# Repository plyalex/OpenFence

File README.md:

#OpenFence
OpenFence is a digital livestock fencing system, which uses GPS and stereo audio alerts to contain animals within a specified boundary. 
The location of the fences can be updated using the web interface, and transferred to collar devices wirelessly using LoRa via the in field base station. 
The movements of the animals are logged and transferred to the web, to allow analysis of movements and land utilisation.
#The Purpose
OpenFence is designed to make it easier to implement productive and environmentally friendly grazing practises, such as cell grazing. 
This style of grazing has been shown to increase biodiversity, ground cover, soil carbon and water retention, however it is not commonly implemented due to the additional expenses of fencing and labour.
#Build Details
Go to the [HackaDay.io Page](https://hackaday.io/project/10725-openfence-digital-livestock-fencing)

#[Collar Code](https://github.com/plyalex/OpenFence/tree/master/software/collar/CollarSoftware)
Download and open with Arduino. Additional libraries required are: [TinyGPS++](https://github.com/mikalhart/TinyGPSPlus/releases) and RTCZero.

#Licence
All files: GNU GPL v3

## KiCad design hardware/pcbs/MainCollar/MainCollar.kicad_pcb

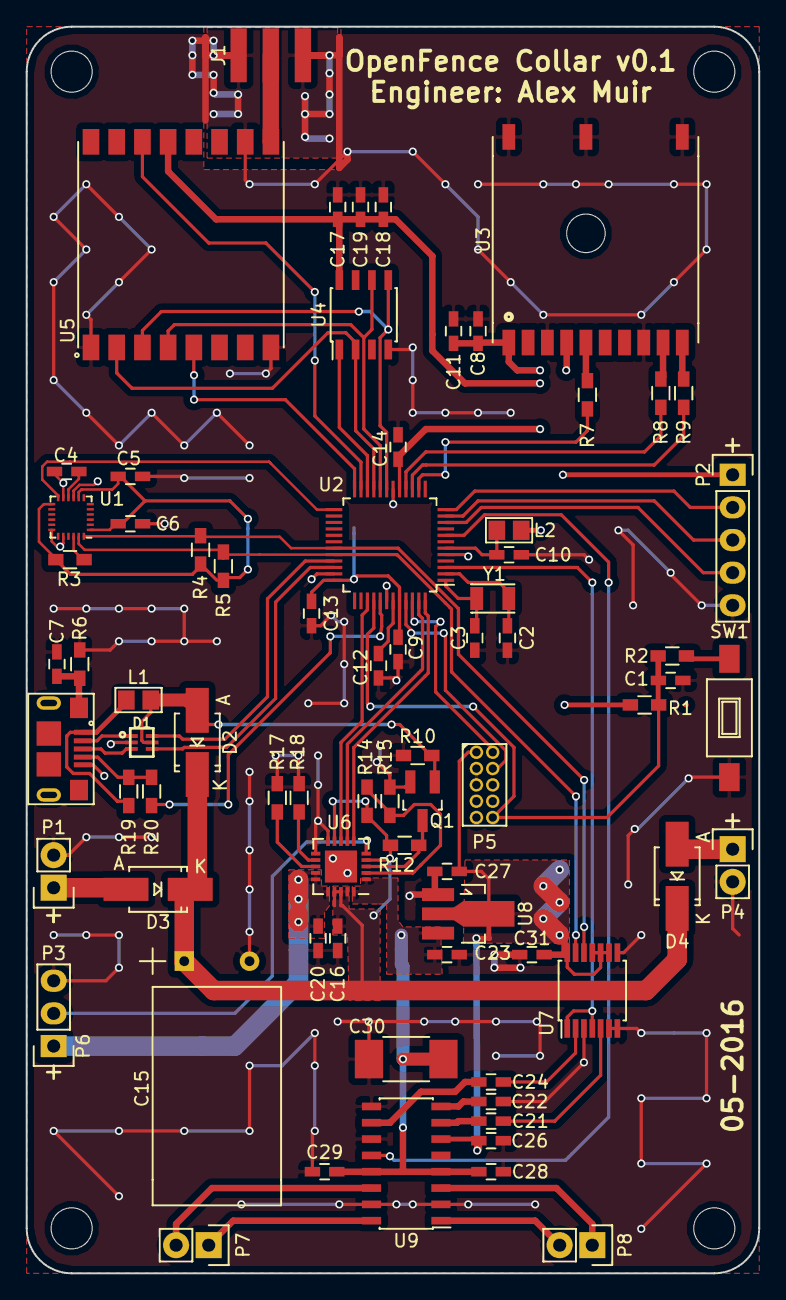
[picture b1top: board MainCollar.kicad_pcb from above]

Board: 2 copper layers, 57.0 x 97.0 mm, 78 parts (0 on the bottom side), 64 nets.

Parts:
C1, C4, C6, C9, C10, C13, C14, C17, C18, C31: 0.1uF; C_0603_HandSoldering
C2, C3: 18pF; C_0603_HandSoldering
C5, C11: 0.01uF; C_0603_HandSoldering
C7, C16, C19, C20, C23: 4.7uF; C_0603_HandSoldering
C8, C12, C22, C26, C27, C28, C29: 1uF; C_0603_HandSoldering
C15: 2200uF; Cap1017
C21, C24: 0.47uF; C_0603_HandSoldering
C30: 47uF; C_1812_HandSoldering
D1: USBLC6-2; SOT666
D2, D3, D4: SS24; SMA_Handsoldering
J1: SMA-EDGE; RF-SMA-EDGE
L1, L2: 600R @ 100MHz; IND-0805
M1, M2, M3, M4: Mounting_Hole; MountingHole_3.2mm_M3
P1: USB_OTG; USB-10118193-0001LF
P2: CONN_01X05; Pin_Header_Straight_1x05
P3: Solar1; Pin_Header_Straight_1x02
P4: Solar2; Pin_Header_Straight_1x02
P5: CONN_02X05; HDR_2x5_Pitch1.27mm
P6: Battery; Pin_Header_Straight_1x03
P7: SPK_L; Pin_Header_Straight_1x02
P8: SPK_R; Pin_Header_Straight_1x02
Q1: 2N7002; SOT-23_Handsoldering
R1, R3, R4, R5, R12: 10K; R_0603_HandSoldering
R2, R20: 330; R_0603_HandSoldering
R6: 1M; R_0603_HandSoldering
R7, R8, R9, R17: 1K; R_0603_HandSoldering
R10, R15, R19: 100K; R_0603_HandSoldering
R14: 270K; R_0603_HandSoldering
R18: 50K; R_0603_HandSoldering
SW1: SW_PUSH; SW_SPST_FSMSM
U1: MPU9250
U2: SAMD21G; TQFP-48_7x7mm_Pitch0.5mm
U3: PA6C
U4: S25FL116K; SOIC-8_3.9x4.9mm_Pitch1.27mm
U5: RF95W; RFM9xW
U6: MCP73871; QFN-20-1EP_4x4mm_Pitch0.5mm
U7: MAX5387; TSSOP-14_4.4x5mm_Pitch0.65mm
U8: MCP1700T-3302E/MB; SOT89-3_Housing_Handsoldering
U9: PAM8403; SOIC-16_3.9x9.9mm_Pitch1.27mm
Y1: 32.768kHz; FC-135

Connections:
+3V3: C5.1, C6.1, C8.1, C9.1, C11.1, C13.1, C14.1, C17.1, C18.1, C19.1, C26.1, C27.1, C31.2, L2.2, P2.1, P5.1, R1.1, R3.1, R4.1, R5.1, U1.1, U1.8, U1.13, U2.17, U2.36, U2.44, U3.1, U3.4, U4.8, U5.13, U7.9, U7.10, U7.11, U7.14, U8.2, U9.6
/AMP_SD: U2.8, U9.12
/AUX_1: P2.4, U2.10
/AUX_2: P2.3, U2.11
/AUX_3: P2.2, U2.12
/AudioIn: U2.3, U7.1, U7.4
/Flash_CS: U2.22, U4.1
/GPS_FIX: R7.1, U2.14
/GPS_RXD: R9.2, U2.15
/GPS_TXD: R8.1, U2.16
/MISO: U2.21, U4.2, U5.2
/MOSI: U2.19, U4.5, U5.3
/MPU_INT: U1.12, U2.25
/RF_CS: U2.24, U5.5
/RF_INT: U2.23, U5.14
/SCK: U2.20, U4.6, U5.4
/SCL: R5.2, U1.23, U2.32, U7.13
/SDA: R4.2, U1.24, U2.31, U7.12
/STAT1: U2.39, U6.8
/STAT2: U2.47, U6.7
/SWDCLK: P5.4, U2.45
/SWDIO: P5.2, U2.46
/USB+: D1.4, U2.34
/USB-: D1.6, U2.33
/USB_ID: R20.1, U2.41
/~PG: U2.48, U6.6
/~RESET~: C1.1, P5.10, R1.2, R2.1, U2.40
GND: C1.2, C2.1, C3.1, C4.2, C5.2, C6.2, C7.2, C8.2, C9.2, C10.2, C11.2, C12.2, C13.2, C14.2, C15.2, C16.2, C17.2, C18.2, C19.2, C20.2, C22.2, C23.2, C26.2, C27.2, C28.2, C29.2, C30.2, C31.1, D1.2, J1.2, J1.3, J1.4, J1.5, P1.5, P2.5, P3.2, P4.2, P5.3, P5.5, P6.3, Q1.2, R6.2, R10.2, R15.2, R17.2, R18.2, SW1.1, U1.9, U1.11, U1.18, U1.20, U2.5, U2.18, U2.35, U2.42, U3.3, U3.8, U3.11, U3.12, U3.13, U4.4, U5.1, U5.8, U5.10, U6.10, U6.11, U6.21, U7.3, U7.6, U7.7, U7.8, U8.1, U9.2, U9.9, U9.11, U9.15
unnamed: C2.2, U2.2, Y1.1
unnamed: C3.2, U2.1, Y1.2
unnamed: C4.1, U1.10
unnamed: C7.1, P1.6, R6.1
unnamed: C10.1, L2.1, U2.6
unnamed: C12.1, U2.43
unnamed: C21.1, U9.7
unnamed: C21.2, U7.5
unnamed: C22.1, U9.8
unnamed: C24.1, U9.10
unnamed: C24.2, U7.2
unnamed: D1.1, P1.2
unnamed: D1.3, P1.3
unnamed: D3.2, P3.1
unnamed: D4.2, P4.1
unnamed: J1.1, U5.9
unnamed: P1.4, R19.1, R20.2
unnamed: P6.2, U6.5
unnamed: P7.1, U9.16
unnamed: P7.2, U9.14
unnamed: P8.1, U9.3
unnamed: P8.2, U9.1
unnamed: Q1.3, R12.2, U6.3
unnamed: R2.2, SW1.2
unnamed: R3.2, U1.22
unnamed: R7.2, U3.5
unnamed: R8.2, U3.9
unnamed: R9.1, U3.10
unnamed: R14.2, R15.1, U6.2
unnamed: R17.1, U6.13
unnamed: R18.1, U6.12
VBAT: C20.1, P6.1, U6.14, U6.15, U6.16
VBUS: D1.5, D2.2, L1.2, Q1.1, R10.1
VCC: C15.1, C16.1, D2.1, D3.1, D4.1, R12.1, R14.1, U6.4, U6.9, U6.17, U6.18, U6.19
VOUT: C23.1, C28.1, C29.1, C30.1, U6.1, U6.20, U8.3, U9.4, U9.13
VUSB: L1.1, P1.1, R19.2

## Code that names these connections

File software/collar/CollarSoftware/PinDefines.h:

#ifndef PinDefines_h
#define PinDefines_h
	#include "Geofence.h"

	//I2C Addresses: MPU 0x68, POT 0x2F
	//GPS_TX, RX = Serial1
	//Serial Monitor = SerialUSB

	#define DAC_OUT     A0
	#define AMP_EN      A2
	#define AUX_0       9
	#define AUX_1       8
	#define AUX_2       A4
	#define GPS_FIX     3
	#define FLASH_CS    ATN
	#define RF_INT      2
	#define RF_CS       5
	#define MPU_INT     11
	#define CHARGE_S1   26 //PIN_LED_TXL
	#define CHARGE_S2   A5
	#define CHARGE_PG   25 //PIN_LED_RXL

	#define GPSSerial 	Serial1
	
	//Global Variables - Updatable in Web Interface
	extern uint8_t NODE_ADDRESS;
	extern uint8_t distThresh;
	extern uint8_t motionThresh;
	extern bool testing;
	extern int16_t magbias0;
	extern int16_t magbias1;
	extern int16_t magbias2;

	extern uint8_t polyCorners;
    extern struct position fencePoints[256];
    extern uint8_t fenceversion;

#endif

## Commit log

2016-04-21 Initial commit.
2016-04-21 Added links
2016-04-22 Added compiled file to the git ignore
2016-05-12 Schematics almost complete
2016-05-12 Creating an Arduino library for the PA6C GPS
2016-05-14 Initial PCB component placement
2016-05-16 PCB Prototype Completed
2016-05-18 Initial prototype design ready for 3D printing.
2016-05-20 Version 2 renders
2016-05-26 Second version ready for 3D printing.
2016-05-26 Renders for displaying the PCB
2016-05-26 Initial Commit of the geofence library
2016-05-26 Moving from doubles to floats
2016-08-14 Initial Commit of Web App
2016-08-14 Updating for mistakes
2016-08-14 Updating for custom PCB
2016-08-15 Added Tilt corrected compass heading.
    Using the function getHeading() will return a float value of the
    compass heading adjusted based on the accelerometer orientation.
2016-08-15 Ignore temporary files
2016-08-15 Added bearing2fence function
    bearing2fence() returns the Azimuth between the closest point on the
    fence and the collar device.
2016-08-28 Updating Collar firmware
    Added ability to update fence locations over LoRa.
    Using PWM output for the audio alert.
    Updated the Geofence functionality such that it returns the side
    outside, the distance outside and the bearing of the fence to the
    collar.
2016-08-28 Initial Commit of baseStation Arduino code
2016-08-28 Python Script to get/post to the database to/from serial
2016-08-28 Altering the models that are used for the database collections.
2016-08-30 Depreciated the use of the PA6C library in favour of the TinyGPS++ library
2016-08-30 Removing irrelevant comments
2016-08-30 wakeOnmotion function fixed
2016-09-05 Ignore .DS_Store
2016-09-05 Switched R17 and R18 to be in correct locations
2016-09-05 Implemented Send to Devices button
2016-09-05 Added Refresh function
2016-09-06 Custom Board Testing - Using OSCULP32K as clock
2016-09-06 Changed zip location URL
2016-09-06 Fixed size and checksum
2016-09-06 Rezip
2016-09-06 Removed __MACOSX from Zip
2016-09-19 Added Collar settings page
2016-09-19 Send settings over LoRa added
2016-09-19 Basestation solid works design
2016-09-19 Update board settings from LoRa packet
2016-09-20 Added storing to Flash functionality
    In the event of power loss the collar can use the values that were last
    stored in flash.
2016-09-20 Tweaking outputs, struct sizes, removing some depreciated code.
2016-09-20 Fixing issues with settings transfer
    Due to structs padding to the nearest 16 bits there were issues with
    alignment of memcpy calls
2016-09-20 Update RF_ID from Website now works
    Both the sending address and receiving address needed to update:
    radio.setHeaderFrom(NODE_ADDRESS);
    manager.setThisAddress(NODE_ADDRESS);
2016-09-29 Bug fixes, cleaning up code.
2016-09-29 Cleaning up
2016-09-29 Fixed issue where an even number of fence locations didn't set the last packet flag
2016-10-03 Fixed sleep mode exiting immediately
    Need to ensure that the UART/I2C communications have completed before
    sleeping. Add a 100mSec delay before sleep solves this.
2016-10-03 Cleaning old code and adding comments
2016-10-09 Create readme file.
2016-10-28 Increased LUT to have 101 values so the [100] is addressable.
    And fixed up some comments
2016-10-28 Solved geofence issue where direction was backwards.
2016-10-28 Testing function for the geofence software.
2016-10-28 Removed averaging of magnetometer
    Makes the function faster, it wasn’t really improving the smoothness of
    the output.
2016-10-28 Ignore binaries
2016-10-28 Code clean up, remove redundant and commented code.
2016-10-28 Fixed mag calibration saving to flash issue.
2016-10-28 Fixed settings saving to flash function
2016-10-28 Updating for use on RPi
2016-11-10 Final Report
